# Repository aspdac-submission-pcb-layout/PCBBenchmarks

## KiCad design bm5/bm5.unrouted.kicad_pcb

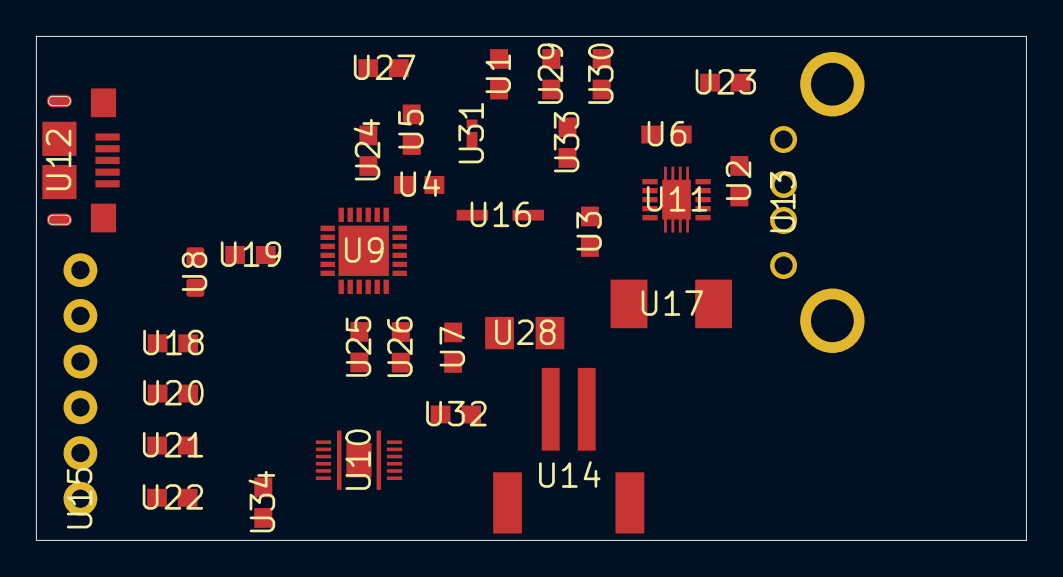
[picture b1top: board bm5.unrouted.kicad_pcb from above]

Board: 2 copper layers, 55.0 x 28.0 mm, 34 parts (0 on the bottom side), 27 nets, no tracks yet.

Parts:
U1, U2, U3, U4, U5, U6, U7, U18, U19, U20, U21, U22, U23, U24, U25, U26, U27, U29, U30, U32, U33, U34: 0603
U8: LED-0603
U9: QFN50P400X400X100-25N
U10: BQ27441DRZRG1A
U11: SON50P300X300X100-11N
U12: 10118193-0001LF
U13: UE27AC54100
U14: JST-2-SMD
U15: 1X06
U16: INDPM3630X200N
U17: INDPM5552X200N
U28: 1206
U31: DSN2_1

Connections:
3.3V: U15.5, U18.2, U20.2, U21.2, U22.2
5V: U2.1, U11.3, U11.4, U11.7, U13.1, U23.1, U33.2
/CHG_INT: U9.7, U15.2, U21.1
/FUEL_INT: U10.12, U15.1, U22.1
/REG: U5.1, U9.22, U24.1
/SCL: U9.5, U10.2, U15.4, U18.1
/SDA: U9.6, U10.1, U15.3, U20.1
/VBAT_CELL: U7.1, U9.13, U9.14, U10.7, U28.1
/VBAT_MAIN: U3.1, U8.A, U9.8, U9.15, U9.16, U11.9, U11.10, U16.2, U17.1
GND: U1.2, U2.2, U3.2, U5.2, U6.2, U7.2, U9.17, U9.18, U9.25, U10.3, U10.13, U11.GND@1, U11.GND@2, U11.GND@3, U11.GND@4, U11.GND@5, U11.GND@6, U11.GND@7, U11.GND@8, U11.GND@9, U12.GND, U12.SHIELD$1, U12.SHIELD$2, U12.SHIELD$3, U12.SHIELD$4, U13.4, U13.5, U13.6, U14.1, U15.6, U25.1, U26.1, U27.1, U29.2, U30.2, U32.1, U34.2
unnamed: U4.1, U9.19, U9.20, U16.1, U31.2
unnamed: U4.2, U9.21
unnamed: U1.1, U9.23, U29.1, U30.1, U31.1, U33.1
unnamed: U6.1, U11.6
unnamed: U10.5, U34.1
unnamed: U8.C, U19.1
unnamed: U9.1, U12.VCC
unnamed: U9.2, U12.D+
unnamed: U9.3, U12.D-
unnamed: U9.4, U19.2
unnamed: U9.9, U25.2
unnamed: U9.10, U26.2
unnamed: U9.11, U24.2, U27.2
unnamed: U10.6, U10.8, U14.2, U28.2
unnamed: U10.10, U32.2
unnamed: U11.1, U11.2, U17.2
unnamed: U11.5, U23.2

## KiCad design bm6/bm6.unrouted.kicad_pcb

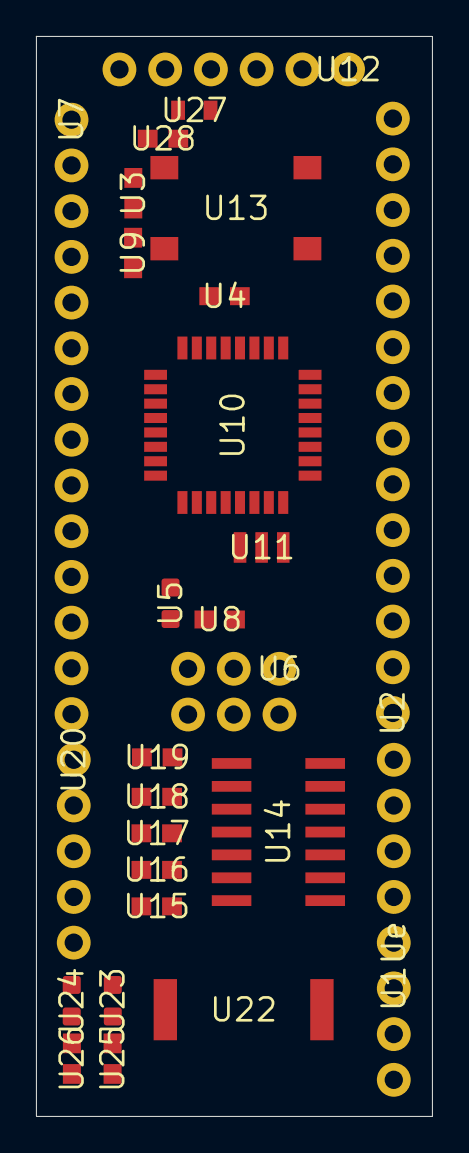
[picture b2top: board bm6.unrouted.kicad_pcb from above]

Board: 2 copper layers, 22.0 x 60.0 mm, 28 parts (0 on the bottom side), 51 nets, no tracks yet.

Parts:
U1: 1X03
U2, U7: 1X14
U3, U4, U8, U9, U15, U16, U17, U18, U19, U25, U26, U28: 0603
U5, U23, U24: LED-0603
U6: 2X3
U10: TQFP32-08
U11: RESONATOR-SMD
U12: FTDI_BASIC
U13: TACTILE_SWITCH_SMD_6.2MM_TALL
U14: SO14
U20: 1X05
U22: PKMCS
U27: FUSC1608X100N
Ue: 1X05

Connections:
/A0: U7.7, U10.23
/A1: U7.8, U10.24
/A2: U7.9, U10.25
/A3: U7.10, U10.26
/A4: U7.11, U10.27
/A5: U7.12, U10.28
/A6: U7.13, U10.19
/A7: U7.14, U10.22
/D2: U2.3, U10.32
/D3: U2.4, U10.1
/D4: U2.5, U10.2
/D5: U2.6, U10.9
/D6: U2.7, U10.10
/D7: U2.8, U10.11
/D8: U2.9, U10.12
/D9: U2.10, U10.13
/D10: U2.11, U10.14
/DTR: U3.1, U12.DTR
/GO: U14.3, Ue.1
/MISO: U2.13, U6.1, U10.16
/MOSI: U2.12, U6.4, U10.15
/OUT1: U14.8, Ue.2
/OUT2: U14.7, Ue.3
/OUT3: U14.6, Ue.4
/OUT4: U14.5, Ue.5
/RST: U3.2, U6.5, U9.1, U10.29, U13.B2
/RXI: U7.5, U10.30, U12.TXO
/SCK: U2.14, U6.3, U8.1, U10.17
/TXO: U7.6, U10.31, U12.RXI
GND: U2.2, U4.2, U5.C, U6.6, U7.4, U10.3, U10.5, U10.21, U11.2, U12.GND, U13.A2, U14.14, U22.1, U23.C, U24.C, U28.2
unnamed: U4.1, U10.20
unnamed: U5.A, U8.2
unnamed: U23.A, U25.1
unnamed: U24.A, U26.1
unnamed: U12.VCC, U27.1
unnamed: U14.9, U19.2
unnamed: U14.10, U18.2
unnamed: U14.11, U17.2
unnamed: U14.12, U16.2
unnamed: U14.13, U15.2
unnamed: U19.1, U20.1
unnamed: U18.1, U20.2
unnamed: U17.1, U20.3
unnamed: U16.1, U20.4
unnamed: U15.1, U20.5
unnamed: U1.1, U22.2
unnamed: U1.2, U25.2
unnamed: U1.3, U26.2
unnamed: U10.7, U11.3
unnamed: U10.8, U11.1
VCC: U2.1, U6.2, U7.1, U7.2, U7.3, U9.2, U10.4, U10.6, U10.18, U14.1, U14.2, U14.4, U27.2, U28.1

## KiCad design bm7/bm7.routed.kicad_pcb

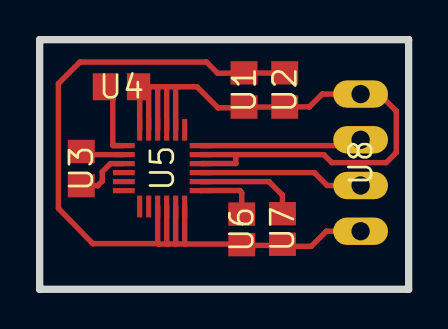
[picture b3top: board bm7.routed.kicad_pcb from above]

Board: 2 copper layers, 20.5 x 13.9 mm, 8 parts (0 on the bottom side), 9 nets.

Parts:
U1, U2, U3, U4: C0805
U5: LGA-24
U6, U7: R0805
U8: MA04-1

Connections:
/SCL: U5.21, U8.2
/SDA: U5.24, U8.3
GND: U1.2, U2.2, U4.1, U5.2, U5.3, U5.4, U5.5, U5.6, U5.22, U5.23, U8.4
unnamed: U3.1, U5.9
unnamed: U3.2, U5.8
unnamed: U4.2, U5.7
unnamed: U5.19, U6.1
unnamed: U5.20, U7.1
VDD: U1.1, U2.1, U5.15, U5.16, U5.17, U5.18, U6.2, U7.2, U8.1

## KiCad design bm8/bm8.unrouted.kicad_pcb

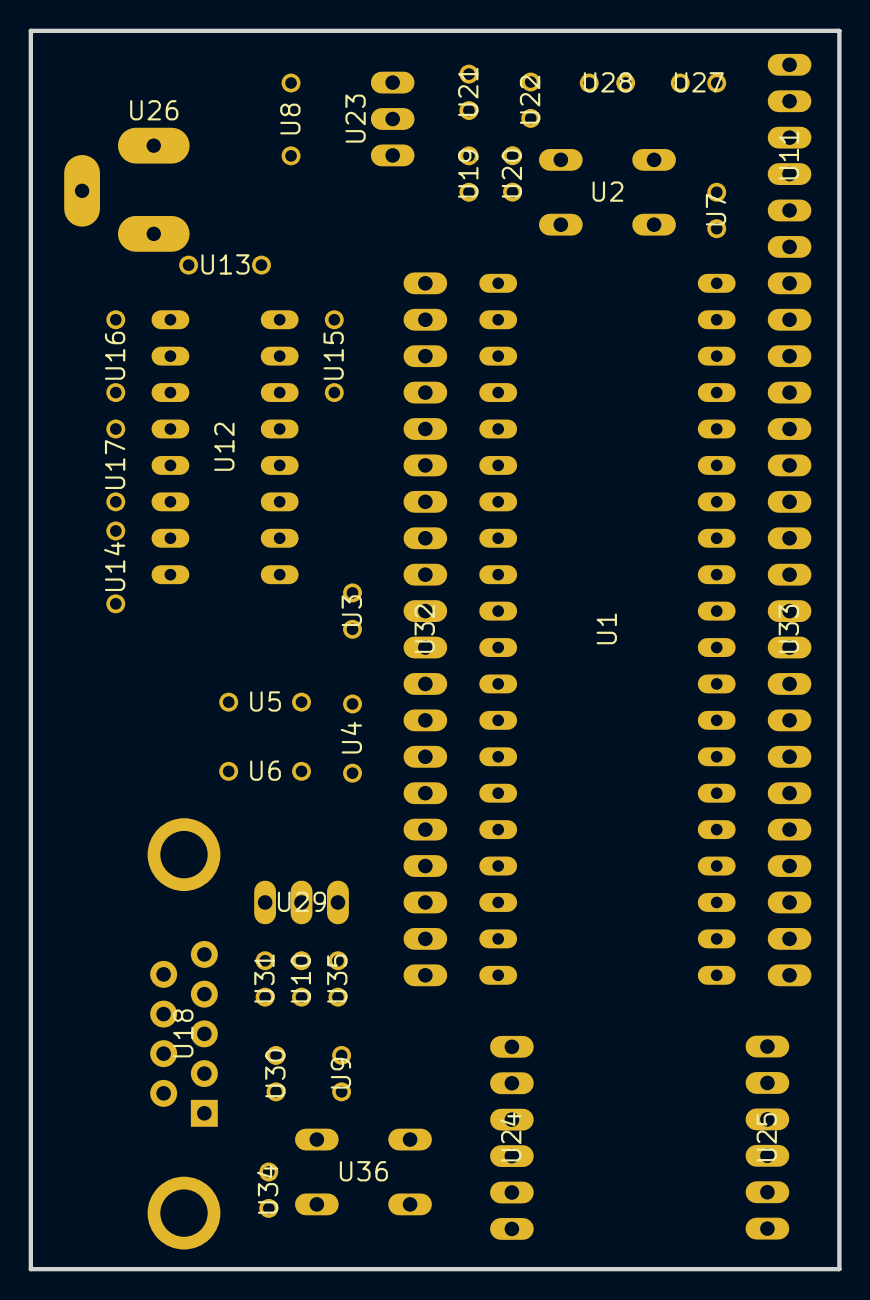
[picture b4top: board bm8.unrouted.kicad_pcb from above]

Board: 2 copper layers, 56.4 x 86.4 mm, 36 parts (0 on the bottom side), 58 nets, no tracks yet.

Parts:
U1: DIL40
U2, U36: B3F-10XX
U3, U22: C025-024X044
U4: HC49_S
U5, U6, U13, U14, U15, U16, U17: C050-024X044
U7, U10, U19, U20, U21, U28, U31, U34, U35: V526-0
U8: C050-025X075
U9, U27, U30: LED3MM
U11, U24, U25: 1X06
U12: DIL16
U18: DB9
U23: 317TS
U26: 733980-62
U29: MA03-1
U32, U33: MA20-1

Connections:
/3.3V_SRC: U1.11, U1.32, U3.1, U7.1, U11.2, U12.16, U13.2, U15.1, U21.2, U22.1, U23.2, U24.3, U28.1, U32.10, U33.9, U36.1
/MRF_CS: U1.17, U24.5, U32.4
/MRF_INT: U1.34, U25.3, U33.7
/MRF_RESET: U1.15, U25.5, U32.6
/MRF_SCK: U1.18, U25.1, U32.3
/MRF_SDI: U1.23, U24.6, U33.18
/MRF_SDO: U1.24, U25.2, U33.17
/MRF_WAKE: U1.16, U25.4, U32.5
/N$17: U1.26, U12.9, U33.15
/N$21: U1.25, U12.10, U33.16
/OS1: U1.13, U4.1, U5.1, U32.8
/OSC2: U1.14, U4.2, U6.1, U32.7
GND: U1.12, U1.31, U2.1, U3.2, U5.2, U6.2, U8.2, U9.K, U11.3, U12.15, U14.1, U15.2, U18.5, U20.1, U22.2, U24.1, U24.2, U25.6, U26.1, U27.K, U30.K, U32.9, U33.10, U34.2
unnamed: U12.2, U13.1
unnamed: U12.6, U14.2
unnamed: U12.1, U16.1
unnamed: U12.3, U16.2
unnamed: U12.4, U17.1
unnamed: U12.5, U17.2
unnamed: U8.1, U23.3, U26.2
unnamed: U12.7, U18.2
unnamed: U12.8, U18.3
unnamed: U1.1, U2.3, U7.2, U11.1, U32.20
unnamed: U1.2, U32.19
unnamed: U1.3, U32.18
unnamed: U1.4, U32.17
unnamed: U1.5, U32.16
unnamed: U1.6, U32.15
unnamed: U1.7, U32.14
unnamed: U1.8, U32.13
unnamed: U1.9, U32.12
unnamed: U1.10, U32.11
unnamed: U1.19, U32.2
unnamed: U1.20, U32.1
unnamed: U1.21, U33.20
unnamed: U1.22, U33.19
unnamed: U1.27, U33.14
unnamed: U1.28, U33.13
unnamed: U1.29, U33.12
unnamed: U1.30, U33.11
unnamed: U1.33, U33.8
unnamed: U1.35, U33.6
unnamed: U1.36, U33.5
unnamed: U1.37, U33.4
unnamed: U1.38, U33.3
unnamed: U1.39, U11.5, U33.2
unnamed: U1.40, U11.4, U33.1
unnamed: U19.2, U21.1, U23.1
unnamed: U27.A, U28.2
unnamed: U30.A, U31.2
unnamed: U9.A, U10.2
unnamed: U34.1, U35.2, U36.3
unnamed: U29.3, U35.1
unnamed: U10.1, U29.2
unnamed: U29.1, U31.1
unnamed: U19.1, U20.2
unnamed: U18.1, U18.4, U18.6
unnamed: U18.7, U18.8
